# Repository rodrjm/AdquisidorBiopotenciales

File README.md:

# Adquisidor de Biopotenciales con ADS131E08

Este proyecto consiste en un sistema de adquisición de biopotenciales utilizando el convertidor analógico a digital (ADC) ADS131E08 de Texas Instruments. El sistema permite adquirir y visualizar señales de biopotenciales en tiempo real a través de una interfaz gráfica en Python.

## Descripción

El proyecto se compone de dos partes principales:

1.  **Firmware (C):**
    * Implementado en C para la placa EDU-CIAA-NXP.
    * Configura y controla el ADS131E08 a través de comunicación SPI.
    * Adquiere datos de biopotenciales y los envía a través de comunicación UART.
    * Proporciona una interfaz de usuario básica para controlar la adquisición y configuración del ADC.
2.  **Software (Python):**
    * Implementado en Python utilizando las bibliotecas `serial`, `numpy` y `pyqtgraph`.
    * Recibe los datos de biopotenciales a través del puerto serial.
    * Procesa y visualiza los datos en tiempo real en una interfaz gráfica.

## Estructura de archivos

* `adquisidorBiopotenciales.c`: Contiene la función principal y la inicialización del hardware.
* `adquisidorBiopotenciales.h`: Declaraciones para `adquisidorBiopotenciales.c`.
* `ADS131E08.c`: Implementación de las funciones para controlar el ADS131E08.
* `ADS131E08.h`: Declaraciones para `ADS131E08.c`.
* `funcionamiento.c`: Lógica principal del sistema (menú, adquisición de datos, etc.).
* `funcionamiento.h`: Declaraciones para `funcionamiento.c`.
* `GPIO.c`: Implementación de las funciones para controlar los GPIO.
* `GPIO.h`: Declaraciones para `GPIO.c`.
* `SPI.c`: Implementación de las funciones para controlar la comunicación SPI.
* `SPI.h`: Declaraciones para `SPI.c`.
* `UART.c`: Implementación de las funciones para controlar la comunicación UART.
* `UART.h`: Declaraciones para `UART.c`.
* `adquisidorDatos.py`: Script de Python para recibir y visualizar los datos.

## Requisitos

* **Hardware:**
    * Placa EDU-CIAA-NXP.
    * ADS131E08.
    * Display de 10 LEDs (opcional).
* **Software:**
    * CIAA-Launcher (disponible en: [https://github.com/epernia/software/releases/tag/r1.1.0](https://github.com/epernia/software/releases/tag/r1.1.0)).
    * Python 3.x.
    * Bibliotecas de Python: `serial`, `numpy`, `pyqtgraph`, `PyQt6`.

## Instalación

1.  **Firmware:**
    * Compila el código C utilizando el Embedded IDE de CIAA-Launcher, o otro IDE de su preferencia.
    * Carga el firmware en la placa EDU-CIAA-NXP.
2.  **Software:**
    * Instala las bibliotecas de Python necesarias:

    \`\`\`bash
    pip install pyserial numpy pyqtgraph PyQt6
    \`\`\`

## Uso

1.  Conecta el ADS131E08 a la placa EDU-CIAA-NXP y los sensores de biopotenciales a las entradas del ADC.
2.  Conecta la placa EDU-CIAA-NXP a tu computadora a través de un puerto serial.
3.  Ejecuta el script de Python `adquisidorDatos.py`.
4.  Utiliza la interfaz de usuario en la placa EDU-CIAA-NXP para controlar la adquisición y configuración del ADC.
5.  Visualiza las señales de biopotenciales en la interfaz gráfica.

## Mejoras

* Implementar un modo de USB más rápido para aprovechar la potencia del sensor.
* Implementar un filtrado digital de las señales.
* Agregar más opciones de configuración a través de la interfaz de usuario.
* Mejorar la interfaz gráfica con más funcionalidades.
* Agregar manejo de errores del ADC.
* Modularizar el código C para mejor mantenibilidad.
* Agregar documentación detallada del código.

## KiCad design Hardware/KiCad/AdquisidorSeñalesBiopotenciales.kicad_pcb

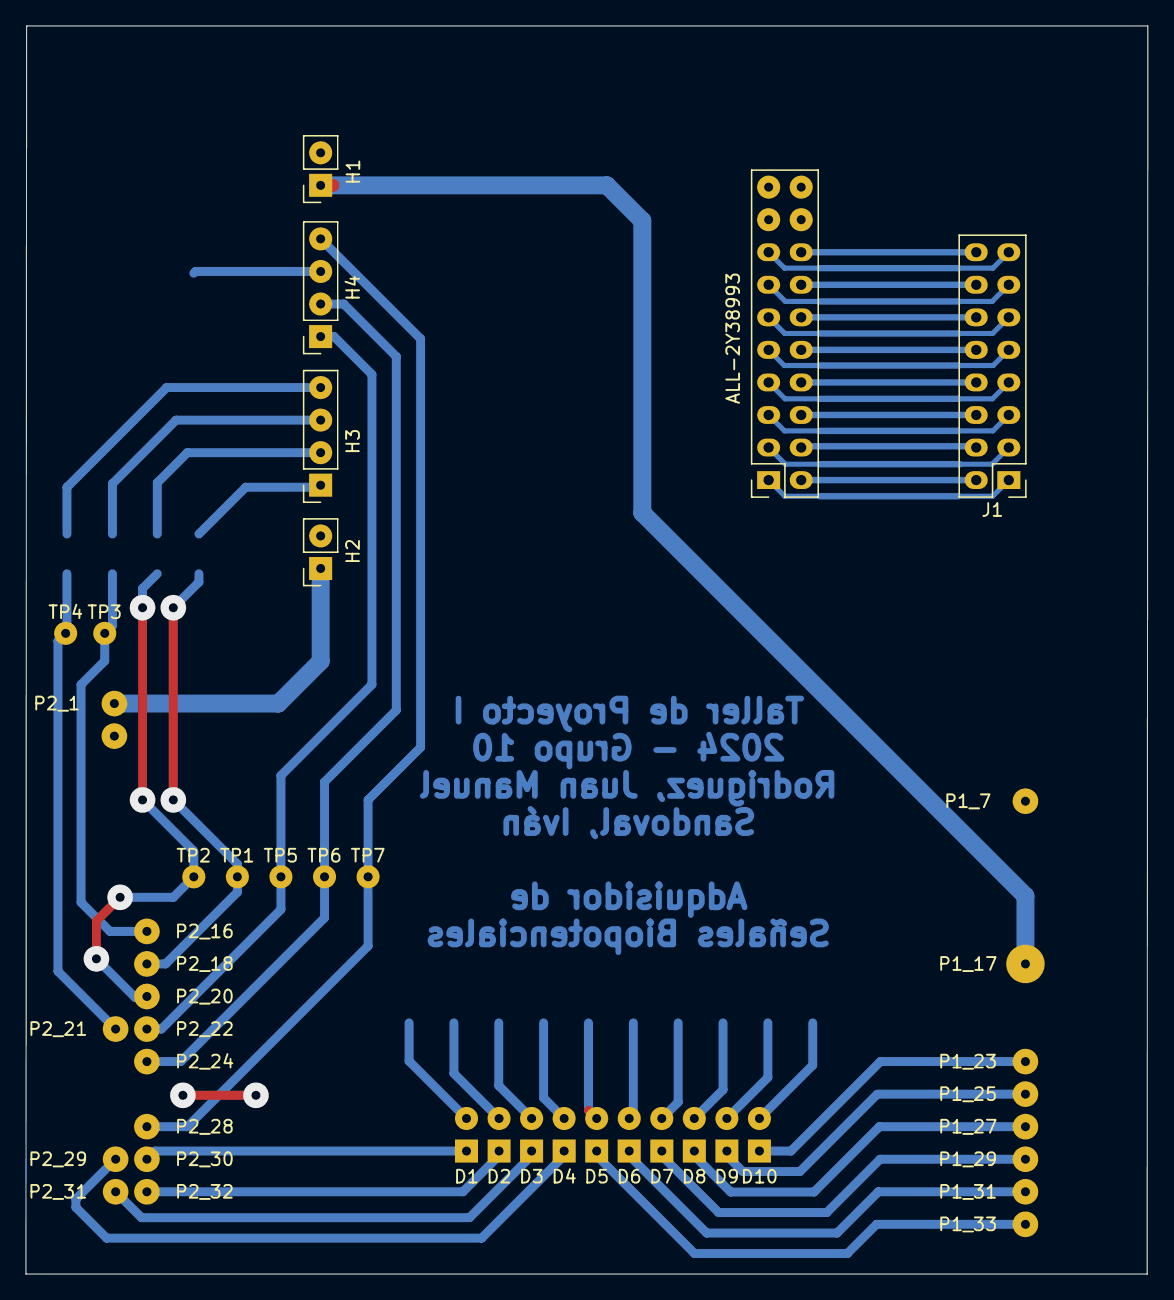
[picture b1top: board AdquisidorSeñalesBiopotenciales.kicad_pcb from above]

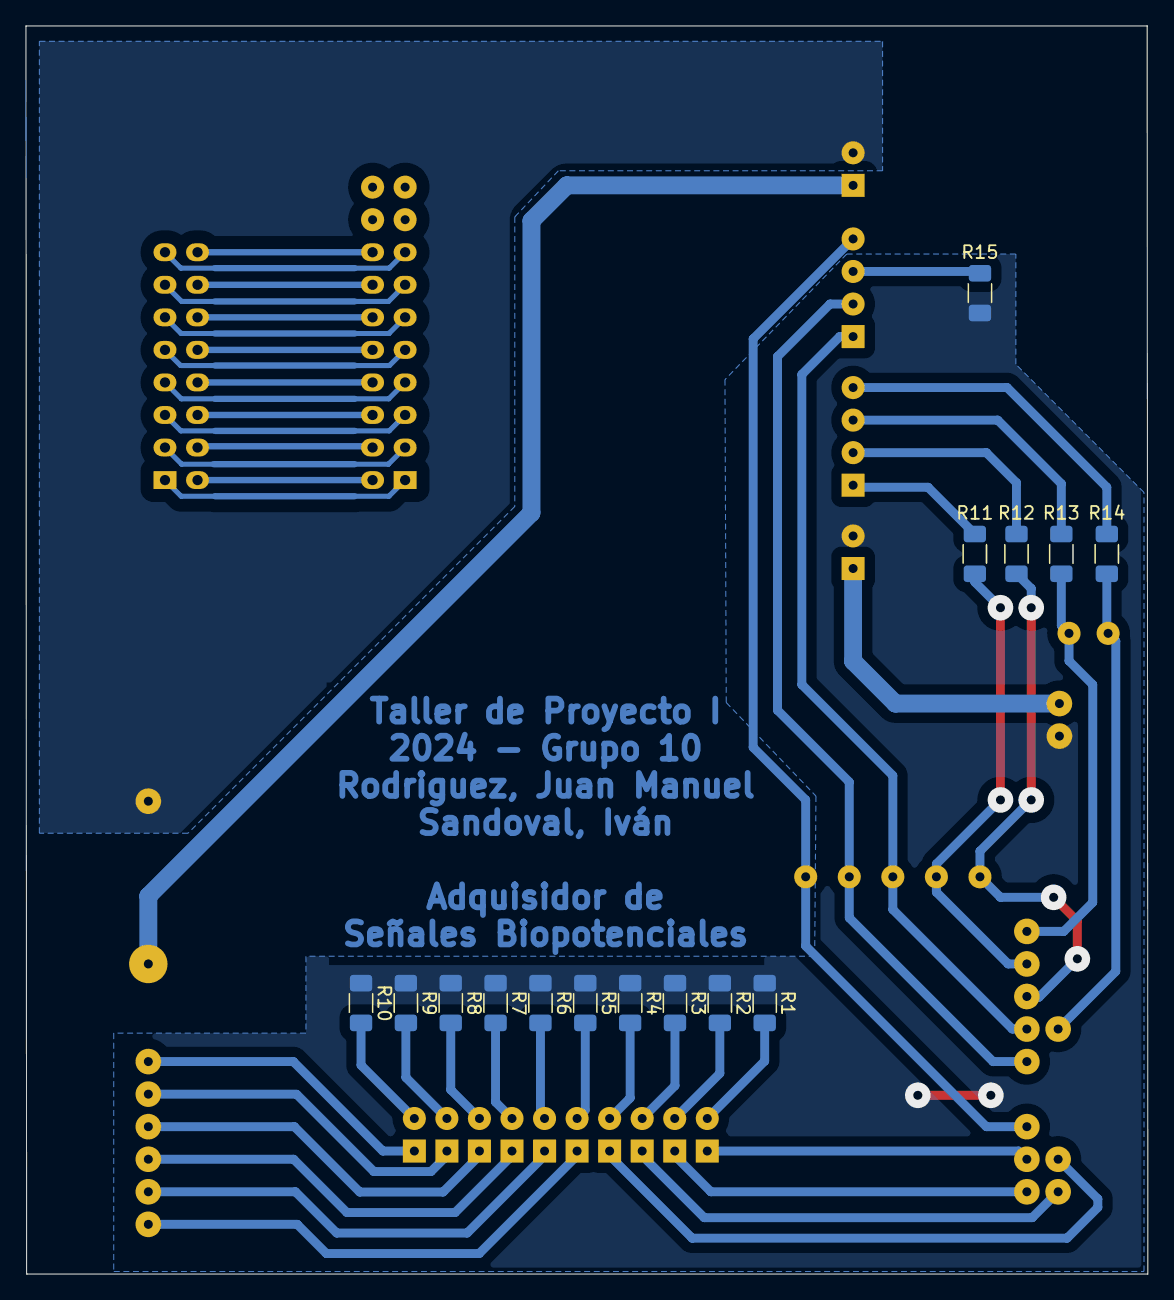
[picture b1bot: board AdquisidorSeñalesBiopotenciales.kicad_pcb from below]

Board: 2 copper layers, 87.6 x 97.4 mm, 59 parts (36 on the bottom side), 52 nets.

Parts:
ALL-2Y38993: Conn_02x10_Odd_Even; PinSocket_2x10_P2.54mm_Vertical
D1, D2, D3, D4, D5, D6, D7, D8, D9, D10: LED; PinSocket_2x01_P2.54mm_Vertical
H1, H2: Conn_01x02_Pin; PinSocket_1x02_P2.54mm_Vertical
H3, H4: Conn_01x04_Pin; PinSocket_1x04_P2.54mm_Vertical
J1: Entradas Analógicas; PinHeader_2x08_P2.54mm_Vertical
P1_7, P1_17, P1_23, P1_25, P1_27, P1_29, P1_31, P1_33, P2_1, P2_3, P2_16, P2_18, P2_20, P2_21, P2_22, P2_24, P2_28, P2_29, P2_30, P2_31, P2_32: Conn_01x01_Socket; PinHeader_1x01_P2.54mm_Vertical
R1, R2, R3, R4, R5, R6, R7, R8, R9, R10, R11, R12, R13, R14, R15: R; R_1206_3216Metric_Pad1.30x1.75mm_HandSolder
TP1, TP2, TP3, TP4, TP5, TP6, TP7: TestPoint; TestPoint_THTPad_1.5x1.5mm_Drill0.7mm

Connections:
3V3: H2.1, P2_1.1
CAN_RD: D8.1 (A), P1_27.27
CAN_TD: D7.1 (A), P1_29.29
GND: H2.2, P2_3.3, R1.1, R2.1, R3.1, R4.1, R5.1, R6.1, R7.1, R8.1, R9.1, R10.1, R15.1
GNDA: H1.2, P1_7.7
GPIO0: D4.1 (A), P2_29.29
GPIO1: D2.1 (A), P2_32.32
GPIO2: D3.1 (A), P2_31.31
LCD1: D1.1 (A), P2_30.30
LCD2: H4.4, P2_28.28, TP7.1
LCD4: H4.1, P2_22.22, TP5.1
LCD_RS: H4.2, P2_24.24, TP6.1
unnamed: ALL-2Y38993.1, J1.1
unnamed: ALL-2Y38993.2, J1.2
unnamed: ALL-2Y38993.3, J1.3
unnamed: ALL-2Y38993.4, J1.4
unnamed: ALL-2Y38993.5, J1.5
unnamed: ALL-2Y38993.6, J1.6
unnamed: ALL-2Y38993.7, J1.7
unnamed: ALL-2Y38993.8, J1.8
unnamed: ALL-2Y38993.9, J1.9
unnamed: ALL-2Y38993.10, J1.10
unnamed: ALL-2Y38993.11, J1.11
unnamed: ALL-2Y38993.12, J1.12
unnamed: ALL-2Y38993.13, J1.13
unnamed: ALL-2Y38993.14, J1.14
unnamed: ALL-2Y38993.15, J1.15
unnamed: ALL-2Y38993.16, J1.16
unnamed: D1.2 (K), R1.2
unnamed: D2.2 (K), R2.2
unnamed: D3.2 (K), R3.2
unnamed: D4.2 (K), R4.2
unnamed: D5.2 (K), R5.2
unnamed: D6.2 (K), R6.2
unnamed: D7.2 (K), R7.2
unnamed: D8.2 (K), R8.2
unnamed: D9.2 (K), R9.2
unnamed: D10.2 (K), R10.2
unnamed: H3.1, R11.2
unnamed: H3.2, R12.2
unnamed: H3.3, R13.2
unnamed: H3.4, R14.2
unnamed: H4.3, R15.2
RS232_RX: D10.1 (A), P1_23.23
RS232_TX: D9.1 (A), P1_25.25
SPI_MISO: P2_18.18, R11.1, TP1.1
SPI_MOSI: P2_21.21, R14.1, TP4.1
SPI_SCK: P2_20.20, R12.1, TP2.1
TCOL1: D6.1 (A), P1_31.31
TFIL0: D5.1 (A), P1_33.33
TXD1: P2_16.16, R13.1, TP3.1
VDDA: H1.1, P1_17.17

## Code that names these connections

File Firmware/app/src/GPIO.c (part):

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   /* Mapeo de los pines del puerto GPIO. */

   /* TRUE (1) para salida, FALSE (0) para entrada. */
   Chip_SCU_PinMux(4, 5, MD_PUP | MD_EZI | MD_ZI, FUNC0); // Mapeo GPIO2[5] en P4_5 RESET (Salida).      -------- PIN LCD2 ----------
   Chip_GPIO_SetPinDIR(LPC_GPIO_PORT, 2, 5, 1);        // Establecer RESET como Salida.                  
   Chip_SCU_PinMux(4, 8, MD_PUP | MD_EZI | MD_ZI, FUNC0); // Mapeo GPIO5[12] en P4_8 PWDN (Salida).      -------- PIN LCD_RS ----------
   Chip_GPIO_SetPinDIR(LPC_GPIO_PORT, 5, 12, 1);       // Establecer PWDN como Salida.
   Chip_SCU_PinMux(4, 10, MD_PUP | MD_EZI | MD_ZI, FUNC4); // Mapeo GPIO5[14] en P4_10 DRDY (Entrada).   -------- PIN LCD4 ----------
   Chip_GPIO_SetPinDIR(LPC_GPIO_PORT, 5, 14, 0);       // Establecer DRDY como Entrada.
   Chip_SCU_PinMux(1, 20, MD_PUP | MD_EZI | MD_ZI, FUNC0); // Mapeo GPIO0[15] en P1_20 CS (Salida).      -------- PIN ENET_TXD1 ----------
   Chip_GPIO_SetPinDIR(LPC_GPIO_PORT, 0, 15, 1);       // Establecer CS como Salida.

   // PIN UTILIZADO PARA DEBUG.
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   Chip_GPIO_SetPinDIR(LPC_GPIO_PORT, 5, 13, 1);

   /* LEDs. */
   Chip_SCU_PinMux(4, 4, MD_PUP | MD_EZI | MD_ZI, FUNC0); // Mapeo GPIO2[4] en P4_4 LED1 (Salida). -------- PIN LCD1 ----------
   Chip_GPIO_SetPinDIR(LPC_GPIO_PORT, 2, 4, 1);  // Establecer LED1 como Salida.
   Chip_SCU_PinMux(6,4,MD_PUP|MD_EZI|MD_ZI,FUNC0); // Mapeo GPIO3[3] en P6_4 LED2 (Salida).	      -------- PIN GPIO1 ----------
   Chip_GPIO_SetPinDIR(LPC_GPIO_PORT,3,3,1);		// Establecer LED2 como Salida.
   Chip_SCU_PinMux(6,5,MD_PUP|MD_EZI|MD_ZI,FUNC0); // Mapeo GPIO3[4] en P6_5 LED3 (Salida).        -------- PIN GPIO2 ----------
   Chip_GPIO_SetPinDIR(LPC_GPIO_PORT,3,4,1);		// Establecer LED3 como Salida
   Chip_SCU_PinMux(6,1,MD_PUP|MD_EZI|MD_ZI,FUNC0); // Mapeo GPIO3[0] en P6_1 LED4 (Salida).	      -------- PIN GPIO0 ----------
   Chip_GPIO_SetPinDIR(LPC_GPIO_PORT,3,0,1);		// Establecer LED4 como Salida
   Chip_SCU_PinMux(4,0,MD_PUP|MD_EZI|MD_ZI,FUNC0); // Mapeo GPIO2[0] en P4_0 LED5 (Salida).        -------- PIN TFIL0 ----------
   Chip_GPIO_SetPinDIR(LPC_GPIO_PORT,2,0,1);		// Establecer LED5 como Salida
   Chip_SCU_PinMux(7,4,MD_PUP|MD_EZI|MD_ZI,FUNC0); // Mapeo GPIO3[12] en P7_4 LED6 (Salida).       -------- PIN TCOL1 ----------
   Chip_GPIO_SetPinDIR(LPC_GPIO_PORT,3,12,1);		// Establecer LED6 como Salida
   Chip_SCU_PinMux(3,2,MD_PUP|MD_EZI|MD_ZI,FUNC4); // Mapeo GPIO5[9] en P3_2 LED7 (Salida).        -------- PIN CAN_TD ----------
   Chip_GPIO_SetPinDIR(LPC_GPIO_PORT,5,9,1);		// Establecer LED7 como Salida
   Chip_SCU_PinMux(3,1,MD_PUP|MD_EZI|MD_ZI,FUNC4); // Mapeo GPIO5[8] en P3_1 LED8 (Salida).	      -------- PIN CAN_RD ----------
   Chip_GPIO_SetPinDIR(LPC_GPIO_PORT,5,8,1);		// Establecer LED8 como Salida
   Chip_SCU_PinMux(2,3,MD_PUP|MD_EZI|MD_ZI,FUNC4); // Mapeo GPIO5[3] en P2_3 LED9 (Salida).        -------- PIN RS232_TX ----------
   Chip_GPIO_SetPinDIR(LPC_GPIO_PORT,5,3,1);		// Establecer LED9 como Salida
   Chip_SCU_PinMux(2,4,MD_PUP|MD_EZI|MD_ZI,FUNC4); // Mapeo GPIO5[4] en P2_4 LED10 (Salida).       -------- PIN RS232_RX ----------
   Chip_GPIO_SetPinDIR(LPC_GPIO_PORT,5,4,1);		// Establecer LED10 como Salida
}

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
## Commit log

2024-11-25 Commit inicial + add gitignore
    Add gitignore
2024-11-25 Commit inicial
    Commit inicial
2024-11-25 Modificacion velocidad UART y configuracion para muestreo 1kSPS
2024-11-25 Hojas de datos y archivos de KiCad
2024-11-25 Correccion archivos KiCad
2024-11-27 separacion de funciones
    Se separo la función de test y la de lectura de datos
2024-11-27 archivo de matlab
    Se agrego el archivo de matlab
2024-11-28 Agregacion de funcionamiento de leds y teclas
2024-11-28 modificacion Matlab
    se modifico el archivo de Matlab
2024-11-29 Correccion ecuacion del archivo de Matlab y ajustes en el funcionamiento del display
2024-11-29 Modificaciones varias
    Correccion del efecto rebote de los pulsadores
    Correccion del funcionamiento de los pulsadores y los leds
    Modificacion del funcionamiento general del sistema
    Modificacion del archivo de muestra en matlab
2024-12-02 modificación lectura de datos
    Se modifico la función de lectura de datos, y la del funcionamiento en general. Además se modifico la secuencia de encendido de los LEDs.
2024-12-02 Arreglos menores
    Eliminación de archivos que sobraban
2024-12-05 modificación matlab
    Se modifico el código de Matlab para poder visualizar la señal en el tiempo .
2024-12-09 Agregación de selección de modo para las señales
    Y actualización en el código de Matlab, intentando de que la gráfica se muestre más rápida
2024-12-11 Actualizacion de gitignore y adicion de byte de arranque
2024-12-11 Primera version del adquisidor de datos en Python
2024-12-11 Actualización del archivo de Python para que tome bien los valores negativos
2024-12-11 Arreglos en el funcionamiento del display de LEDs
2024-12-12 Optimización del código
2024-12-16 Correccion de muestra de datos
2024-12-19 señal Cuadrada y Triangular de prueba
    Se agregaron dos funciones, una para generar una señal cuadrada de -3mv a 3mv, y la otra para generar una señal triangular.
2025-02-14 Modificaciones finales
2025-02-23 Ajustes finales
    Actualización de comentarios generales del código y README.md
